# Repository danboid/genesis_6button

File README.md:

# Six button Sega Mega Drive / Genesis controller board

This repository contains a KiCad project for a six button Sega Mega Drive / Genesis controller board as well as ATTiny404 micro controller code to implement a replacement for the 6 button Sega Mega Drive controller's custom chip. This board is also compatible with the ZX Spectrum Next and its clones.

**Note: the `main` HEAD is not necessarily tested! Tested revisions of the board+firmware will be tagged**

## How do I program the controller?

**DISCLAIMER: This project is provided "as is" for educational purposes only. The authors shall not be held liable for any damage to equipment, data loss, or personal injury incurred through the assembly or use of this project. Proceed at your own risk.**

The ATtiny404 uses UPDI (Unified Program and Debug Interface) for programming, not ISP like older AVR MCUs. 

There are several ways to program the ATtiny404 but probably the most affordable way is to use **avrdude** with a USB serial adapter. serialupdi mode has been supported by **avrdude** since v7.

You will need the following:

* A USB serial adapter such as the [FTDI FT232](https://www.amazon.co.uk/dp/B07BBPX8B8)
* A 4.7 KOhm resistor. A resistor in the range of 3.3K to 10KOhm should be fine if you don't have a 4.7KOhm resistor.
* 5x female to female jumper (DuPont) wires.

The +5V and GND headers are wired directly from the serial adapter to the UPDI header. You must create a "Y" jumper cable that connects both the RX and TX pins on your serial adapter to the single UPDI pin on the controller PCB.

The UPDI pin is the bottom left UPDI header pin that has the square footprint in this schematic screenshot. The resistor needs to be connected to the TX wire of your Y cable. Ensure that your serial adapter voltage selection header is set to 5V.

You should only need to have the ATtiny and the UPDI header soldered to the PCB to program it.

Once you have the board connected as shown above, you can program the firmware under Linux using:

```
avrdude  -p t404 -c serialupdi -P /dev/ttyUSB0 -U flash:w:main.hex
```

Or under Windows:

```
avrdude.exe -p t404 -c serialupdi -P COM6 -U flash:w:main.hex
```

Make sure you set the serial port device correctly by checking **dmesg** output under Linux or **Device Manager** under Windows.

## Building a joystick

The cable is connected to the J2 header using this pinout:

Pin 1 on J2 and all of the chips is marked on the PCB silkscreen with a small white dot to the side of pin 1.

Here's photo of this board wired up to a Sanwa clone joystick and housed within a 3D printed [Uzebox fightstick](https://uzebox.org/wiki/Joystick) case:

## Credits

Schematic and ATtiny code by [R.F.Merrill](https://github.com/rfmerrill)

Silkscreen and documentation by [Dan MacDonald](https://github.com/danboid/)

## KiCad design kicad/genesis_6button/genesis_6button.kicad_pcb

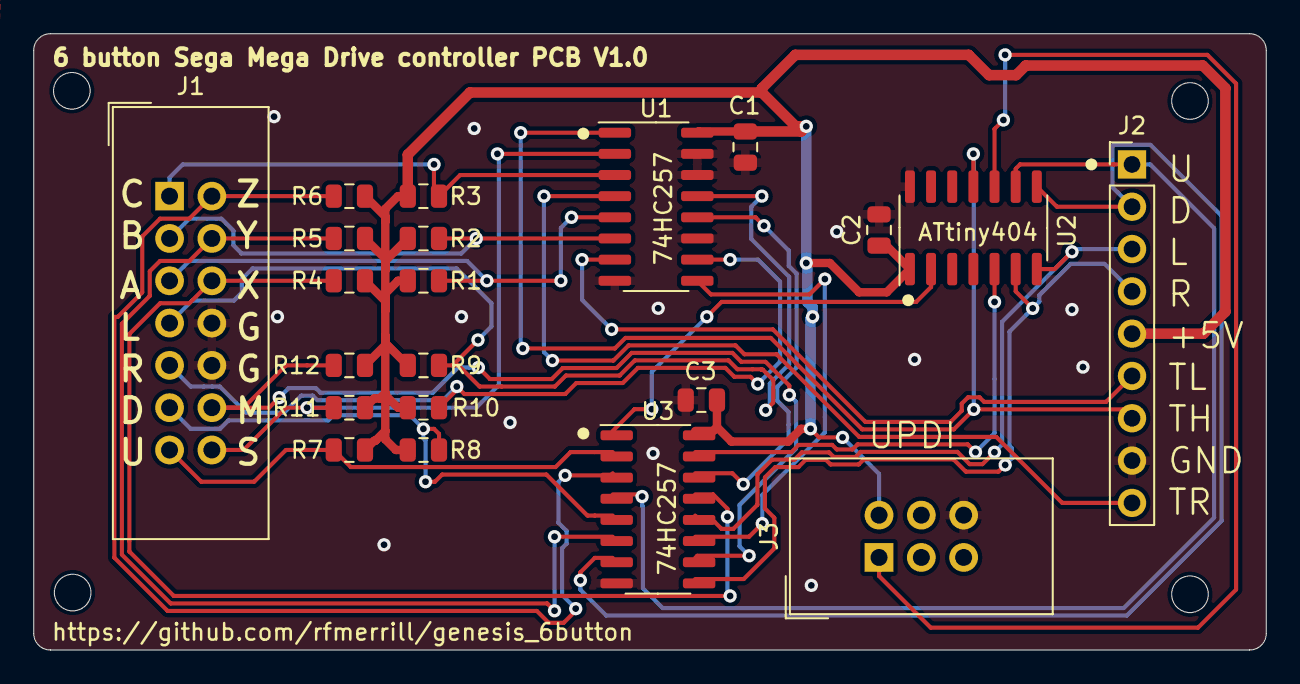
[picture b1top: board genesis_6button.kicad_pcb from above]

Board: 2 copper layers, 74.0 x 37.0 mm, 25 parts (0 on the bottom side), 26 nets.

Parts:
C1, C2, C3: 0.1u; C_0805_2012Metric
H1, H2, H3, H4: MountingHole; MountingHole_2.2mm_M2
J1: Conn_02x07_Odd_Even; IDC-Header_2x07_P2.54mm_Vertical
J2: DB9_Female; PinHeader_1x09_P2.54mm_Vertical
J3: Conn_02x03_Odd_Even; IDC-Header_2x03_P2.54mm_Vertical
R1, R2, R3, R4, R5, R6, R7, R8, R9, R10, R11, R12: 75k; R_0805_2012Metric
U1, U3: 74HC257; SOIC-16_3.9x9.9mm_P1.27mm
U2: ATtiny404-SS; SOIC-14_3.9x8.7mm_P1.27mm

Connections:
+5V: C1.1, C2.1, C3.1, J2.5, J3.2, R1.1, R2.1, R3.1, R4.1, R5.1, R6.1, R7.1, R8.1, R9.1, R10.1, R11.1, R12.1, U1.16 (VCC), U2.1 (VCC), U3.16 (VCC)
BUTTON_A: J1.5, R1.2, U1.5 (I0b)
BUTTON_B: J1.3, R2.2, U1.6 (I1b)
BUTTON_C: J1.1, R3.2, U1.3 (I1a)
BUTTON_DOWN: J1.11, R8.2, U3.5 (I0b)
BUTTON_LEFT: J1.7, R9.2, U1.13 (I1c)
BUTTON_MODE: J1.12, R12.2, U3.10 (I1d)
BUTTON_RIGHT: J1.9, R10.2, U1.10 (I1d)
BUTTON_START: J1.14, R11.2, U1.2 (I0a)
BUTTON_UP: J1.13, R7.2, U3.2 (I0a)
BUTTON_X: J1.6, R4.2, U3.13 (I1c)
BUTTON_Y: J1.4, R5.2, U3.6 (I1b)
BUTTON_Z: J1.2, R6.2, U3.3 (I1a)
DOWN: J2.2, U2.8 (PB1), U3.7 (Zb)
GND: C1.2, C2.2, C3.2, J1.8, J1.10, J2.8, J3.6, U1.8 (GND), U1.11 (I0d), U1.14 (I0c), U1.15 (OE), U2.14 (GND), U3.8 (GND)
LEFT: J2.3, U2.7 (PB2), U3.12 (Zc)
unnamed: J3.1, U2.10 (~RESET/PA0)
unnamed: U1.12 (Zc), U3.14 (I0c)
unnamed: U1.9 (Zd), U3.11 (I0d)
unnamed: U2.2 (PA4), U3.1 (S)
unnamed: U2.5 (PA7), U3.15 (OE)
RIGHT: J2.4, U2.6 (PB3), U3.9 (Zd)
TH: J2.7, U1.1 (S), U2.11 (PA1)
TL: J2.6, U1.7 (Zb)
TR: J2.9, U1.4 (Za)
UP: J2.1, U2.9 (PB0), U3.4 (Za)

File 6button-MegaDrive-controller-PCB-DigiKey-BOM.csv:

Digi-Key Part Number,Quantity,Reference,Value,Description,Datasheet
478-KGM21NR71H104KTCT-ND,10,"C1,C2,C3",0.1u,CAP CER 0.1UF 50V X7R 0805 – Only 3 needed but cheaper to buy 10 than 3,~
A122908-ND,1,J1,CONN HEADER VERT 14POS 2.54MM,"Connector Header Through Hole 14 position 0.100"" (2.54mm)",~
2057-PH1-09-UA-ND,1,J2,CONN HEADER VERT 9POS 2.54MM,"Connector Header Through Hole 9 position 0.100"" (2.54mm)",~
2057-BHR-06-VUA-ND,1,J3,CONN HEADER VERT 6POS 2.54MM,"Connector Header Through Hole 6 position 0.100"" (2.54mm)",~
A102341CT-ND,12,"R1,R2,R3,R4,R5,R6,R7,R8,R9,R10,R11,R12",75k,"75 kOhms ±0.1% 0.1W, 1/10W Chip Resistor 0805 (2012 Metric) Thin Film",~
296-CD74HC257M96CT-ND,2,"U1,U3",74HC257,Multiplexer 4 x 2:1 16-SOIC,http://www.ti.com/lit/gpn/sn74LS257
ATTINY404-SSNRCT-ND,1,U2,ATTINY404-SSNR,"AVR tinyAVR™ 0, Functional Safety (FuSa) Microcontroller IC 8-Bit 20MHz 4KB (4K x 8) FLASH 14-SOIC",http://ww1.microchip.com/downloads/en/DeviceDoc/50002687A.pdf

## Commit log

2025-10-04 Revert to first revision of PCB
2025-10-04 Move U3 slightly to fix a thermal relief error
2025-10-04 Add extra labels to front silkscreen
2025-10-04 Add version number to front silkscreen
2025-10-04 Add M2 mount holes
2025-10-04 Add buttons to silkscreen
2025-10-04 Add Linux build script for ATtiny404 code
2025-10-04 Use -O3 option for Linux build script to match VisualC project build options
2025-10-04 Round off PCB corners
2025-10-06 Update build script to remove old build files before building
2025-10-06 Add main.hex controller firmware
2025-10-06 Add programming and wiring instructions to README
2025-10-07 Second revision of silkscreen
2025-10-07 Add gerbers zip file for v1.0
2025-10-09 Add DigiKey BOM
2025-10-23 Change avrdude example command in README to use usbtiny config
2025-11-11 Add Arduino project files
2025-11-30 Add tested avrdude instructions and UPDI wiring images
2025-11-30 Add instructions for finding correct serial device
2025-11-30 Add note about required PCB components for programming the ATtiny
2025-12-03 Remove link to old OSHpark board
2025-12-03 Rename MD connector pinout image
2025-12-03 Add csv BOM
2025-12-03 Add credits
2025-12-27 Update README to note the Spectrum Next is compatible
2025-12-27 Update README with a photo of a wired joystick and buttons
2026-02-03 Remove duplicate connector image
2026-02-03 Add Manufacturer and Manufacturer Product Number columns to BOM files
2026-02-03 Add disclaimer to README
2026-02-03 Move images into images subdir
2026-02-03 Tweak build script
2026-02-03 Remove duplicate images from root dir
